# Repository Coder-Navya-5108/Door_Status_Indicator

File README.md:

# Door_Status_Indicator
door status indicator module using kicad

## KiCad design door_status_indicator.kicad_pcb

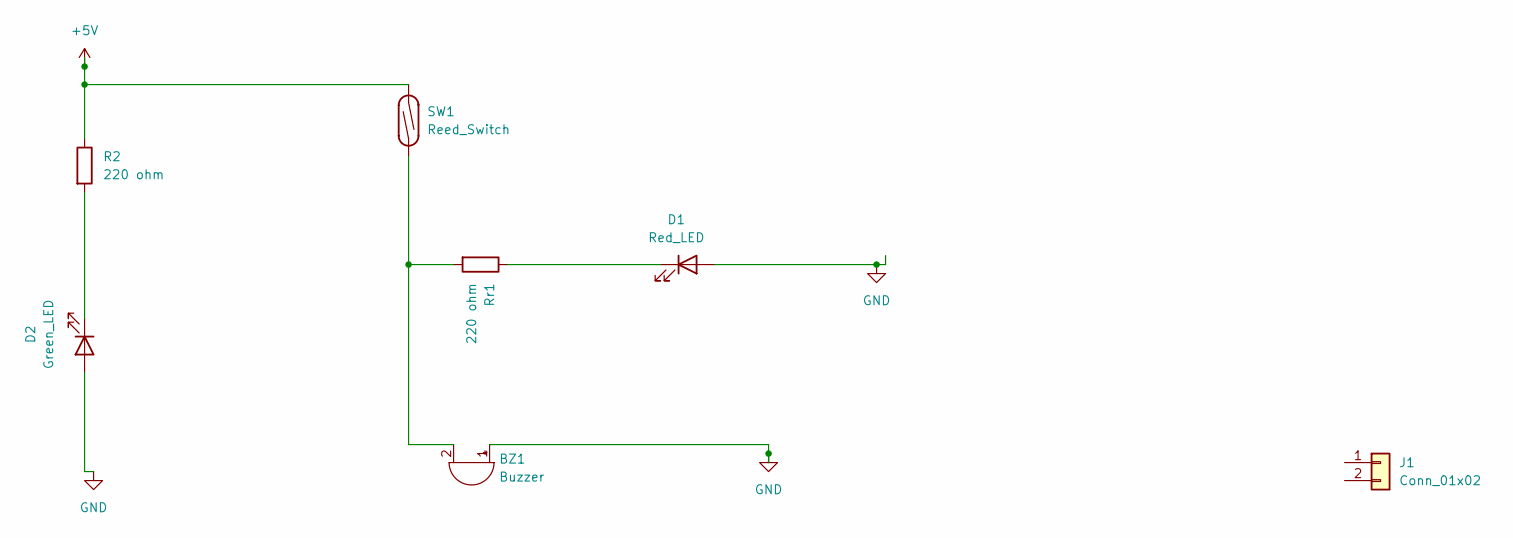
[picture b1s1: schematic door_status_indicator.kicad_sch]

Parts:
BZ1: Buzzer; Buzzer_12x9.5RM7.6
D1: Red_LED; LED_D1.8mm_W1.8mm_H2.4mm_Horizontal_O1.27mm_Z1.6mm
D2: Green_LED; LED_D1.8mm_W1.8mm_H2.4mm_Horizontal_O1.27mm_Z1.6mm
J1: Conn_01x02; TerminalBlock_MaiXu_MX126-5.0-02P_1x02_P5.00mm
R2: 220 ohm; R_Axial_DIN0207_L6.3mm_D2.5mm_P7.62mm_Horizontal
Rr1: 220 ohm; R_Axial_DIN0207_L6.3mm_D2.5mm_P5.08mm_Vertical
SW1: Reed_Switch; PinHeader_1x02_P2.54mm_Vertical

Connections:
+5V: R2.1, SW1.2
GND: BZ1.1 (+), D1.2 (A), D2.2 (A)
unnamed: BZ1.2 (-), Rr1.2, SW1.1
unnamed: D1.1 (K), Rr1.1
unnamed: D2.1 (K), R2.2

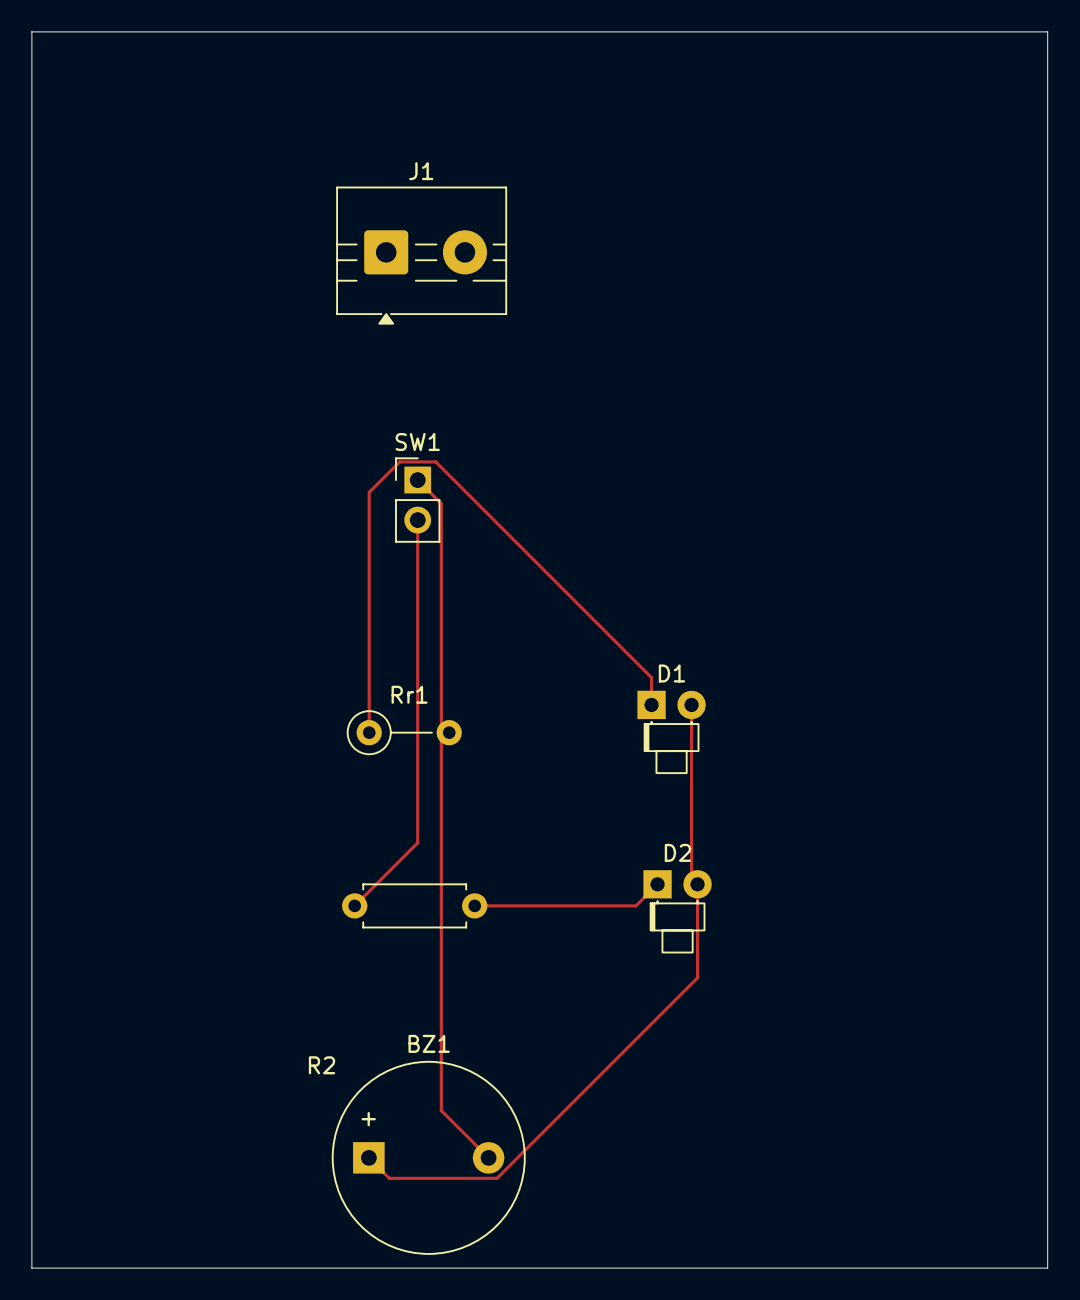
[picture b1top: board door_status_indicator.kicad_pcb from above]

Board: 2 copper layers, 64.5 x 78.5 mm, 7 parts (0 on the bottom side), 5 nets.
